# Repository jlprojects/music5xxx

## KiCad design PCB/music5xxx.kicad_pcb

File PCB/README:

## Music 5xxx clone PCB

Made using Kicad 5.1.2

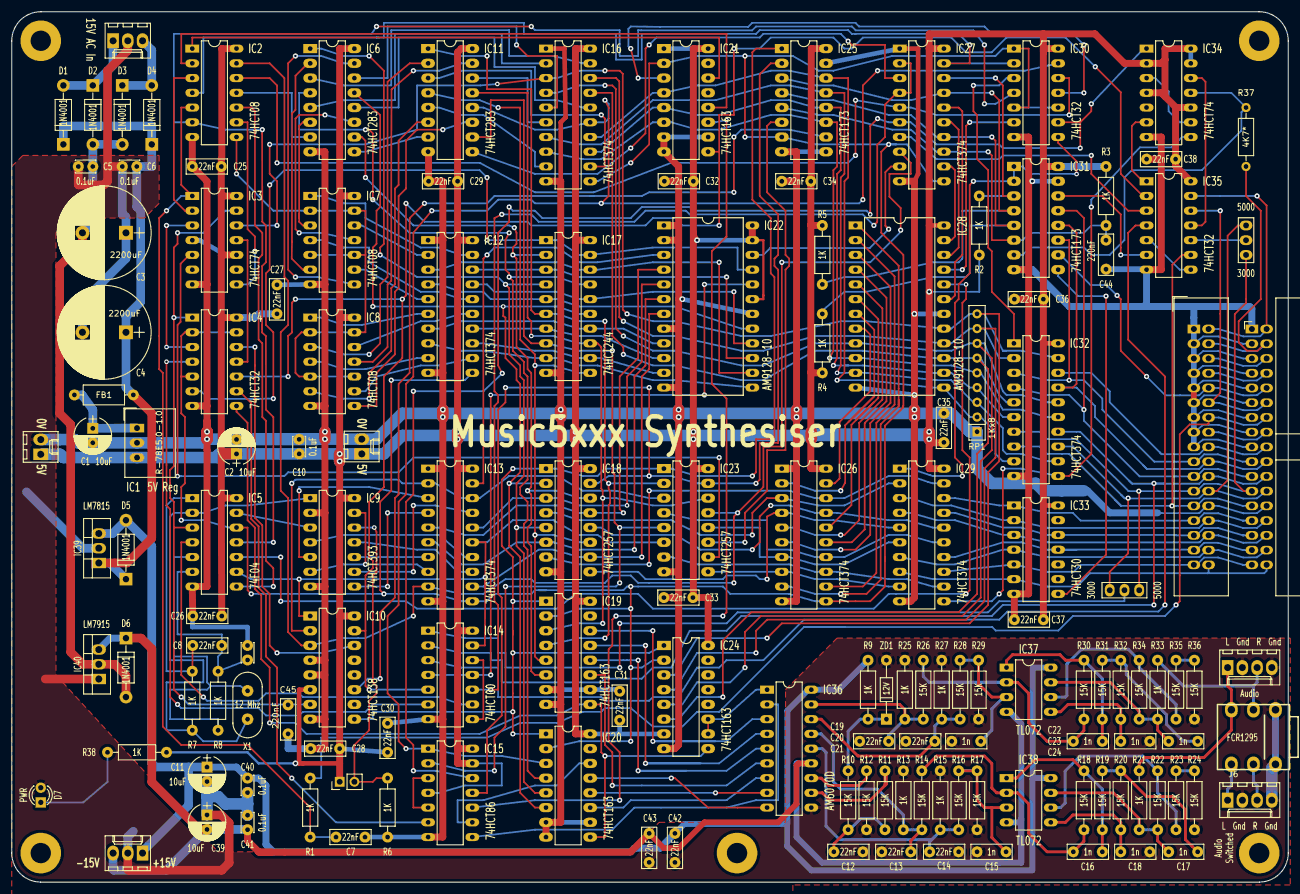
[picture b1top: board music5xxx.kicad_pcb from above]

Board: 2 copper layers, 220.0 x 150.0 mm, 151 parts (0 on the bottom side), 217 nets.

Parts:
C1, C2, C11, C39: 10uF; CP_Radial_D6.3mm_P2.50mm
C3, C4: 2200uF; CP_Radial_D16.0mm_P7.50mm
C5, C6, C10, C40, C41: 0.1uF; C_Disc_D3.4mm_W2.1mm_P2.50mm
C7, C8, C12, C13, C14, C19, C20, C25, C26, C27, C28, C29, C30, C31, C32, C33, C34, C35, C36, C37, C38, C42, C43: 22nF; C_Rect_L7.0mm_W2.5mm_P5.00mm
C9: 33pF; C_Disc_D3.4mm_W2.1mm_P2.50mm
C15, C16, C17, C18, C21, C22, C23, C24: 1n; C_Rect_L7.0mm_W2.5mm_P5.00mm
C44, C45: 220nF; C_Rect_L7.0mm_W2.5mm_P5.00mm
D1, D2, D3, D4, D5, D6: 1N4001; D_DO-41_SOD81_P10.16mm_Horizontal
D7: PWR; LED_D3.0mm
FB1: Ferrite; L_Axial_L7.0mm_D3.3mm_P10.16mm_Horizontal_Fastron_MICC
H1, H2, H3, H4, H5: 3.5mm; MountingHole_3.5mm_Pad
IC1: R-78E5.0-1.0; DCDC-Conv_RECOM_R-78E-0.5
IC2, IC7, IC8: 74HCT08; DIP-14_W7.62mm_LongPads
IC3, IC34: 74HCT74; DIP-14_W7.62mm_LongPads
IC4, IC30, IC35: 74HCT32; DIP-14_W7.62mm_LongPads
IC5: 74F04; DIP-14_W7.62mm_LongPads
IC6, IC11: 74HCT283; DIP-16_W7.62mm_LongPads
IC9: 74HCT393; DIP-14_W7.62mm_LongPads
IC10: 74HCT138; DIP-16_W7.62mm_LongPads
IC12, IC13, IC16, IC26, IC27, IC29, IC32: 74HCT374; DIP-20_W7.62mm_LongPads
IC14: 74HCT00; DIP-14_W7.62mm_LongPads
IC15: 74HCT86; DIP-14_W7.62mm_LongPads
IC17: 74HCT244; DIP-20_W7.62mm_LongPads
IC18, IC23: 74HCT257; DIP-16_W7.62mm_LongPads
IC19, IC20, IC21, IC24: 74HCT163; DIP-16_W7.62mm_LongPads
IC22, IC28: AM9128-10; DIP-24_W15.24mm_LongPads
IC25, IC31: 74HCT173; DIP-16_W7.62mm_LongPads
IC33: 74HCT30; DIP-14_W7.62mm_LongPads
IC36: AM6070D; DIP-18_W7.62mm_LongPads
IC37, IC38: TL072; DIP-8_W7.62mm_LongPads
IC39: LM7815; TO-220-3_Vertical
IC40: LM7915; TO-220-3_Vertical
J1: ACIn; Molex_KK-6410-03_03x2.54mm_Straight
J2, J3: +5V; Molex_KK-6410-02_02x2.54mm_Straight
J4: +/-15V; Molex_KK-6410-03_03x2.54mm_Straight
J5: Audio; Molex_KK-6410-04_04x2.54mm_Straight
J6: AudioSwicthed; Molex_KK-6410-04_04x2.54mm_Straight
J7: FCR1295; Cliff-FCR1295
J11: 1MHzBus1; IDC-Header_2x17_Pitch2.54mm_Straight
J12: 1MHzBus2; IDC-Header_2x17_Pitch2.54mm_Angled
JP1: Jumper; Pin_Header_Straight_1x02_Pitch2.54mm
JP6: opt1; Pin_Header_Straight_1x03_Pitch2.54mm
JP7: opt2; Pin_Header_Straight_1x03_Pitch2.54mm
R1, R2, R3, R4, R5, R6, R7, R8, R9, R13, R15, R21, R25, R27, R33, R38: 1K; R_Axial_DIN0207_L6.3mm_D2.5mm_P10.16mm_Horizontal
R10, R11, R12, R14, R16, R17, R18, R19, R20, R22, R23, R24, R26, R28, R29, R30, R31, R32, R34, R35, R36: 15K; R_Axial_DIN0207_L6.3mm_D2.5mm_P10.16mm_Horizontal
R37: 4K7*; R_Axial_DIN0207_L6.3mm_D2.5mm_P10.16mm_Horizontal
RP1: 1Kx8; R_Array_SIP9
X1: 12 Mhz; Crystal_HC49-U_Vertical
ZD1: 12V; D_DO-35_SOD27_P10.16mm_Horizontal

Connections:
+5V: C2.1, C10.1, C25.1, C26.1, C27.1, C28.1, C29.1, C30.1, C31.1, C32.1, C33.1, C34.1, C35.1, C36.1, C37.1, C38.1, IC1.3, IC2.14, IC3.4, IC3.10, IC3.14, IC4.14, IC5.14, IC6.16, IC7.14, IC8.14, IC9.14, IC10.6, IC10.16, IC11.16, IC12.20, IC13.20, IC14.14, IC15.4, IC15.13, IC15.14, IC16.20, IC17.20, IC18.16, IC19.16, IC20.16, IC21.1, IC21.16, IC22.19, IC22.23, IC22.24, IC23.16, IC24.7, IC24.16, IC25.16, IC26.20, IC27.20, IC28.24, IC29.20, IC30.14, IC31.16, IC32.20, IC33.14, IC34.2, IC34.4, IC34.10, IC34.13, IC34.14, IC35.14, J2.1, J3.1, JP1.1, R2.1, R3.1, R4.1, R5.1, R38.1
+15V: C11.1, C40.1, C42.1, D5.2, IC36.18, IC37.8, IC38.8, IC39.3, J4.1, R9.2
-15V: C39.2, C41.2, C43.2, D6.1, IC36.13, IC37.4, IC38.4, IC40.3, J4.3
/1 MHz Bus/1MHZE: J11.4, J12.4, R37.2
/1 MHz Bus/AUDIO: J11.16, J12.16
/1 MHz Bus/R~W: IC35.13, J11.2, J12.2
/1 MHz Bus/a0: IC29.18, IC33.1, J11.27, J12.27
/1 MHz Bus/a1: IC29.3, IC33.2, J11.28, J12.28
/1 MHz Bus/a2: IC29.17, IC33.12, J11.29, J12.29
/1 MHz Bus/a3: IC29.4, IC33.3, J11.30, J12.30
/1 MHz Bus/a4: IC29.14, IC33.11, J11.31, J12.31
/1 MHz Bus/a5: IC29.7, IC33.4, J11.32, J12.32
/1 MHz Bus/a6: IC29.13, IC33.5, J11.33, J12.33
/1 MHz Bus/a7: IC29.8, IC33.6, J11.34, J12.34
/1 MHz Bus/b0: IC18.7, IC26.18, IC29.19
/1 MHz Bus/b0': IC26.19, IC28.8
/1 MHz Bus/b1: IC18.4, IC26.3, IC29.2
/1 MHz Bus/b1': IC26.2, IC28.7
/1 MHz Bus/b2: IC18.12, IC26.17, IC29.16
/1 MHz Bus/b2': IC26.16, IC28.6
/1 MHz Bus/b3: IC18.9, IC26.4, IC29.5
/1 MHz Bus/b3': IC26.5, IC28.5
/1 MHz Bus/b4: IC23.4, IC26.14, IC29.15
/1 MHz Bus/b4': IC26.15, IC28.4
/1 MHz Bus/b5: IC23.12, IC26.7, IC29.6
/1 MHz Bus/b5': IC26.6, IC28.3
/1 MHz Bus/b6: IC23.7, IC26.13, IC29.12
/1 MHz Bus/b6': IC26.12, IC28.2
/1 MHz Bus/b7: IC23.9, IC26.8, IC29.9
/1 MHz Bus/b7': IC26.9, IC28.1
/1 MHz Bus/b8: C44.1, IC25.5, IC27.13, IC31.6, R3.2
/1 MHz Bus/b9: IC25.4, IC27.14, IC31.5, R4.2
/1 MHz Bus/b10: IC25.3, IC27.17, IC31.4, R5.2
/1 MHz Bus/d0: IC32.18, J11.18, J12.18
/1 MHz Bus/d1: IC31.11, IC32.3, J11.19, J12.19
/1 MHz Bus/d2: IC31.12, IC32.17, J11.20, J12.20
/1 MHz Bus/d3: IC31.13, IC32.4, J11.21, J12.21
/1 MHz Bus/d4: IC14.2, IC32.14, J11.22, J12.22
/1 MHz Bus/d5: IC32.7, J11.23, J12.23, JP6.3, JP7.1
/1 MHz Bus/d6: IC32.13, J11.24, J12.24, JP6.1, JP7.3
/1 MHz Bus/d7: IC32.8, IC35.9, J11.25, J12.25
/1 MHz Bus/~IRQ: J11.8, J12.8
/1 MHz Bus/~NMI: J11.6, J12.6
/1 MHz Bus/~PGFC: IC31.10, J11.10, J12.10
/1 MHz Bus/~PGFD: IC35.12, J11.12, J12.12
/1 MHz Bus/~RST: J11.14, J12.14, R1.1
/+vin: C4.1, C6.1, D1.1, D4.1, D5.1, FB1.2, IC39.1
/-vin: C3.2, C5.2, D2.2, D3.2, D6.2, IC40.2
/AC1: D1.2, D2.1, J1.1
/AC2: D3.1, D4.2, J1.3
/Clock and DAC/i0: IC9.5, IC13.3
/Clock and DAC/i1: IC9.8, IC13.4
/Clock and DAC/i2: IC9.10, IC13.7
/Clock and DAC/i3: IC9.6, IC9.13, IC13.8
/Clock and DAC/i4: IC9.11, IC13.13
/Clock and DAC/i5: IC9.4, IC13.14
/Clock and DAC/i6: IC9.9, IC13.17
/Clock and DAC/mm0: IC12.18, IC17.3, IC22.15
/Clock and DAC/mm1: IC12.17, IC17.16, IC22.16
/Clock and DAC/mm2: IC12.4, IC17.5, IC22.17
/Clock and DAC/mm3: IC12.3, IC17.18, IC22.14
/Clock and DAC/mm4: IC12.8, IC17.9, IC22.13
/Clock and DAC/mm5: IC12.7, IC17.14, IC22.9
/Clock and DAC/mm6: IC12.14, IC17.7, IC22.10
/Clock and DAC/mm7: IC12.13, IC17.12, IC22.11
/Clock and DAC/sm0: IC6.5, IC16.2
/Clock and DAC/sm1: IC6.3, IC16.19
/Clock and DAC/sm2: IC6.14, IC16.5
/Clock and DAC/sm3: IC6.12, IC16.16
/Clock and DAC/sn0: IC6.6, IC7.3
/Clock and DAC/sn1: IC6.2, IC7.6
/Clock and DAC/sn2: IC6.15, IC7.8
/Clock and DAC/sn3: IC6.11, IC7.11
/Clock and DAC/sn4: IC8.6, IC11.6
/Clock and DAC/sn5: IC8.3, IC11.2
/Clock and DAC/sn6: IC8.11, IC11.15
/Clock and DAC/sn7: IC8.8, IC11.11
/Clock and DAC/sp0: IC11.5, IC16.9
/Clock and DAC/sp1: IC11.3, IC16.12
/Clock and DAC/sp2: IC11.14, IC16.6
/L-SW: J6.1, J7.3
/LEFT: J5.1, J7.6, R21.2
/R-SW: J6.3, J7.2
/RIGHT: J5.3, J7.5, R33.2
C4D: IC2.12, IC27.5, IC30.12
CY4: IC11.9, IC27.3
E: IC31.7, IC34.11, R37.1
GND: C1.2, C2.2, C3.1, C4.2, C5.1, C6.2, C7.2, C9.1, C10.2, C11.2, C12.1, C13.2, C14.2, C15.2, C18.1, C19.2, C20.2, C21.2, C24.1, C25.2, C26.2, C27.2, C28.2, C29.2, C30.2, C31.2, C32.2, C33.2, C34.2, C35.2, C36.2, C37.2, C38.2, C39.1, C40.2, C41.1, C42.2, C43.1, C44.2, C45.2, D7.1, IC1.2, IC2.7, IC3.7, IC4.7, IC5.7, IC6.8, IC7.7, IC8.7, IC9.2, IC9.7, IC10.4, IC10.5, IC10.8, IC11.8, IC12.1, IC12.10, IC13.1, IC13.10, IC14.7, IC15.7, IC16.1, IC16.10, IC17.10, IC18.8, IC19.7, IC19.8, IC19.10, IC20.7, IC20.8, IC20.10, IC21.7, IC21.8, IC21.10, IC22.1, IC22.2, IC22.8, IC22.12, IC22.18, IC23.8, IC24.8, IC25.8, IC25.9, IC25.15, IC26.1, IC26.10, IC27.1, IC27.10, IC28.12, IC28.18, IC29.10, IC30.7, IC31.8, IC31.15, IC32.10, IC33.7, IC34.7, IC35.7, IC36.10, IC39.2, IC40.1, J1.2, J2.2, J3.2, J4.2, J5.2, J5.4, J6.2, J6.4, J7.1, J7.4, J11.1, J11.3, J11.5, J11.7, J11.9, J11.11, J11.13, J11.15, J11.17, J11.26, J12.1, J12.3, J12.5, J12.7, J12.9, J12.11, J12.13, J12.15, J12.17, J12.26, R6.2, R12.1, R13.1, R15.1, R17.1, R24.1, R25.1, R27.1, R29.1, R36.1, RP1.1, ZD1.2
INDEX: IC3.5, IC23.10
INVERT: IC15.10, IC21.11
L+: C14.1, IC36.14, R15.2, R16.2
L-: C13.1, IC36.15, R13.2, R14.2
unnamed: C1.1, FB1.1, IC1.1
unnamed: C8.1, C9.2, IC5.6, R8.1
unnamed: C8.2, IC5.1, R7.2
unnamed: C12.2, R10.1, R11.1
unnamed: C15.1, IC38.3, R16.1, R17.2
unnamed: C16.1, IC38.1, R18.1, R19.2
unnamed: C16.2, IC38.2, R14.1, R18.2
unnamed: C17.1, R19.1, R20.2
unnamed: C17.2, IC38.7, R21.1, R22.2
unnamed: C18.2, IC38.5, R20.1
unnamed: C21.1, IC37.3, R28.1, R29.2
unnamed: C22.1, IC37.1, R30.1, R31.2
unnamed: C22.2, IC37.2, R26.1, R30.2
unnamed: C23.1, R31.1, R32.2
unnamed: C23.2, IC37.7, R33.1, R34.2
unnamed: C24.2, IC37.5, R32.1
unnamed: D7.2, R38.2
unnamed: IC2.1, IC21.14
unnamed: IC2.2, IC21.12
unnamed: IC2.3, IC3.2
unnamed: IC2.6, IC5.11, IC30.4
unnamed: IC2.8, IC7.2, IC7.5, IC7.10, IC7.13, IC8.2, IC8.5, IC8.10, IC8.13
unnamed: IC2.9, IC3.8
unnamed: IC2.11, IC6.7
unnamed: IC3.3, IC4.3
unnamed: IC3.11, IC4.11
unnamed: IC5.2, IC9.1, R7.1, X1.1
unnamed: IC5.5, R8.2, X1.2
unnamed: IC5.13, IC9.3
unnamed: IC9.12, JP1.2, R6.1
unnamed: IC6.9, IC11.7
unnamed: IC7.12, IC12.2
unnamed: IC7.9, IC12.5
unnamed: IC8.1, IC12.6
unnamed: IC8.4, IC12.9
unnamed: IC8.9, IC12.12
unnamed: IC8.12, IC12.15
unnamed: IC7.4, IC12.16
unnamed: IC7.1, IC12.19
unnamed: IC14.1, JP7.2
unnamed: IC14.3, IC35.4
unnamed: IC4.4, IC14.6
unnamed: IC5.4, IC14.9
unnamed: IC14.10, IC27.2, IC27.4
unnamed: IC14.4, IC14.11, IC22.20
unnamed: IC15.3, IC15.5
unnamed: IC15.8, IC36.2
unnamed: IC15.9, IC20.14
unnamed: IC4.6, IC17.1, IC17.19, IC22.21
unnamed: IC4.8, IC19.9, IC20.9, IC24.9
unnamed: IC19.11, IC36.6
unnamed: IC19.12, IC36.5
unnamed: IC19.13, IC36.4
unnamed: IC19.14, IC36.3
unnamed: IC20.11, IC36.7
unnamed: IC20.12, IC36.8
unnamed: IC20.13, IC36.9
unnamed: IC21.3, IC30.11
unnamed: IC23.11, IC25.6
unnamed: IC24.10, IC24.11, IC36.1
unnamed: IC27.12, IC28.23
unnamed: IC27.15, IC28.22
unnamed: IC27.16, IC28.19
unnamed: IC5.10, IC28.20
unnamed: IC28.21, IC30.6
unnamed: IC29.1, IC30.8, IC31.1, IC31.2
unnamed: IC30.3, IC32.1
unnamed: IC31.9, IC33.8
unnamed: IC31.14, IC35.6
unnamed: IC34.3, IC34.9
unnamed: IC34.6, IC35.1
unnamed: IC34.12, IC35.11
unnamed: IC35.5, IC35.8
unnamed: IC35.10, JP6.2
unnamed: IC36.11, R11.2
unnamed: IC36.12, R12.2
unnamed: IC37.6, R34.1, R35.2
unnamed: IC38.6, R22.1, R23.2
unnamed: R9.1, R10.2, ZD1.1
unnamed: R23.1, R24.2
unnamed: R35.1, R36.2
PA1: IC13.19, IC22.3
PA2: IC22.22, IC27.9
PROG: IC15.11, IC18.15, IC23.15, IC25.2
R+: C20.1, IC36.16, R27.2, R28.2
R-: C19.1, IC36.17, R25.2, R26.2
SEL: IC29.11, IC32.11, IC34.8
SIGN: IC11.12, IC15.1, IC16.15, IC20.3, IC30.13
addr0: IC5.9, IC10.1, IC13.15, IC14.13, IC23.6
addr1: IC10.2, IC13.2, IC13.18, IC23.3
addr2: IC2.13, IC10.3, IC13.9, IC23.13, IC27.8
addr3: IC13.12, IC18.10, IC22.7
addr4: IC13.6, IC18.6, IC22.6
addr5: IC13.16, IC18.3, IC22.5
addr6: IC13.5, IC18.13, IC22.4
data0: IC3.12, IC16.3, IC24.3, IC28.17, IC32.19, RP1.9
data1: IC16.18, IC24.4, IC28.16, IC32.2, RP1.8
data2: IC16.4, IC24.5, IC28.9, IC32.16, RP1.7
data3: IC16.17, IC24.6, IC28.15, IC32.5, RP1.6
data4: IC16.8, IC21.6, IC25.11, IC28.10, IC32.15, RP1.5
data5: IC16.13, IC21.5, IC25.12, IC28.14, IC32.6, RP1.4
data6: IC16.7, IC25.13, IC28.11, IC32.12, RP1.3
data7: IC16.14, IC21.4, IC25.14, IC28.13, IC32.9, RP1.2
sum0: IC6.4, IC17.17, IC20.4
sum1: IC6.1, IC17.4, IC18.5, IC20.5
sum2: IC6.13, IC17.15, IC18.2, IC20.6
sum3: IC6.10, IC17.2, IC18.14, IC19.6
sum4: IC11.4, IC17.11, IC18.11, IC19.5
sum5: IC11.1, IC17.6, IC19.4, IC23.2
sum6: IC11.13, IC17.13, IC19.3, IC23.14
sum7: IC11.10, IC15.2, IC17.8, IC23.5
~ADDR0: IC2.10, IC5.8
~CRST: C7.1, IC2.5, IC3.1, R1.2
~GATE: IC4.9, IC15.6
~PROG: IC15.12, IC27.6, IC30.9, IC34.1
~REQ: IC27.7, IC35.3
~S0: IC4.10, IC10.15, IC14.5, IC21.9, IC35.2
~S1: IC4.12, IC10.14
~S4: IC10.11, IC25.10
~S6: IC10.9, IC18.1, IC19.1, IC20.1, IC23.1, IC24.1, IC25.1
~S7: C45.1, IC3.13, IC4.1, IC5.3, IC10.7
~SX: IC14.8, IC14.12
~WR: IC2.4, IC27.19, IC30.2
~WRG: IC27.18, IC31.3, R2.2
Ø1: IC4.2, IC4.5, IC4.13, IC5.12, IC12.11, IC13.11, IC16.11, IC19.2, IC20.2, IC21.2, IC24.2, IC25.7, IC26.11, IC27.11, IC30.1, IC30.5, IC30.10
